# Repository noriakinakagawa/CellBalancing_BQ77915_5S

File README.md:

# CellBalancing_BQ77915_5S
5セルリチウム系バッテリのセルバランス＆過電圧過電流低電圧保護＆温度監視付回路。

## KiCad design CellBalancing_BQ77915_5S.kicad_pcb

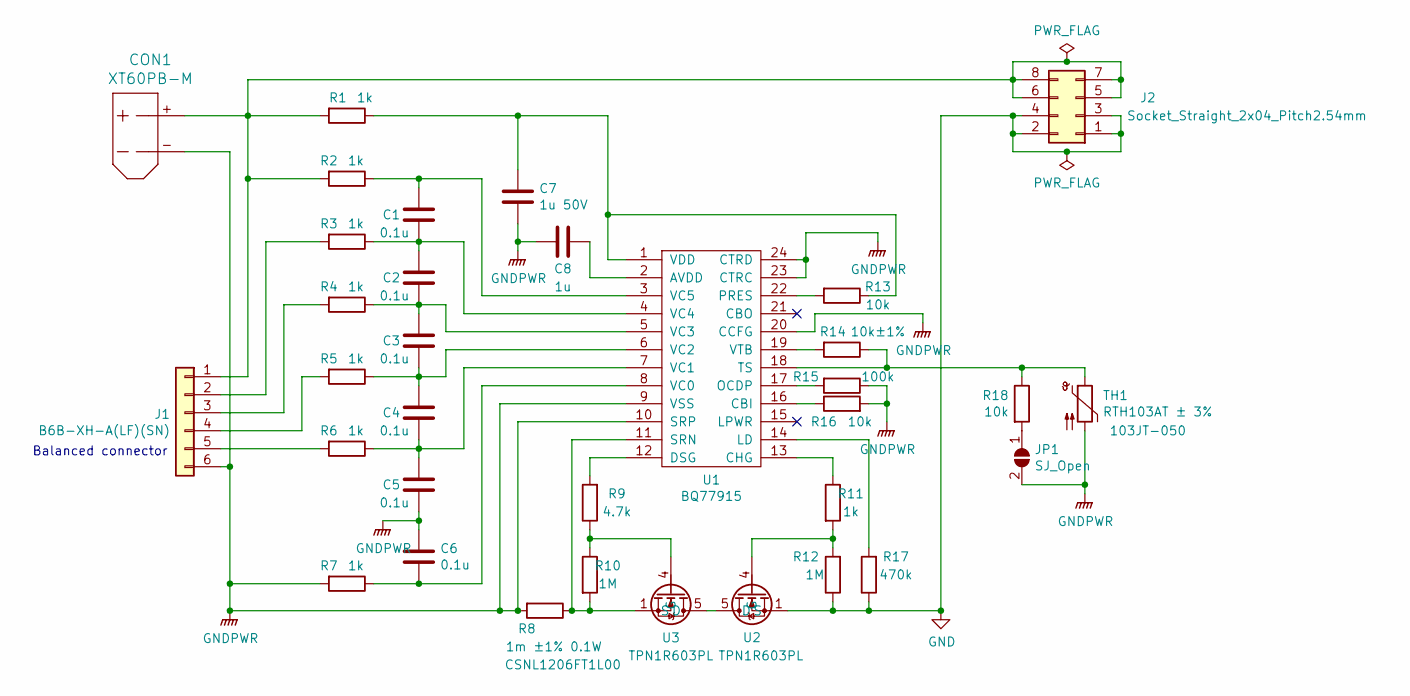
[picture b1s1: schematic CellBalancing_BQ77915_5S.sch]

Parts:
C1, C2, C3, C4, C5, C6: 0.1u; C_0603
C7: 1u 50V; C_0603
C8: 1u; C_0603
CON1: XT60PB-M
J1: B6B-XH-A(LF)(SN); JST_XH_B6B-XH-A_1x06_P2.50mm_Vertical
J2: Socket_Straight_2x04_Pitch2.54mm; Socket_Strip_Straight_2x04_Pitch2.54mm
JP1: SJ_Open; SolderJumper-2_P1.3mm_Open_RoundedPad1.0x1.5mm
R1, R2, R3, R4, R5, R6, R7, R11: 1k; R_0603
R8: 1m ±1% 0.1W; R_1206
R9: 4.7k; R_0603
R10, R12: 1M; R_0603
R13, R16, R18: 10k; R_0603
R14: 10k±1%; R_0603
R15: 100k; R_0603
R17: 470k; R_0603
TH1: RTH103AT ± 3%; SolderJumper-2_P1.3mm_Open_Pad1.0x1.5mm
U1: BQ77915; TSSOP-24_4.4x7.8mm_Pitch0.65mm
U2, U3: TPN1R603PL

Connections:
GND: J2.1, J2.2, J2.3, J2.4, R12.1, R17.1, U2.1 (S), U2.2 (S), U2.3 (S)
GNDPWR: C5.1, C6.1, C7.1, C8.1, CON1.-, J1.6, JP1.2 (B), R7.2, R8.2, R15.1, R16.2, TH1.2, U1.9 (VSS), U1.10 (SRP), U1.20 (CCFG), U1.23 (CTRC), U1.24 (CTRD)
unnamed: C1.1, C2.2, R3.1, U1.4 (VC4)
unnamed: C1.2, R2.1, U1.3 (VC5)
unnamed: C2.1, C3.2, R4.1, U1.5 (VC3)
unnamed: C3.1, C4.1, R5.1, U1.6 (VC2)
unnamed: C4.2, C5.2, R6.1, U1.7 (VC1)
unnamed: C6.2, R7.1, U1.8 (VC0)
unnamed: C7.2, R1.1, R13.1, U1.1 (VDD)
unnamed: C8.2, U1.2 (AVDD)
unnamed: CON1.+, J1.1, J2.5, J2.6, J2.7, J2.8, R1.2, R2.2
unnamed: J1.2, R3.2
unnamed: J1.3, R4.2
unnamed: J1.4, R5.2
unnamed: J1.5, R6.2
unnamed: JP1.1 (A), R18.2
unnamed: R9.2, U1.12 (DSG)
unnamed: R9.1, R10.1, U3.4 (G)
unnamed: R8.1, R10.2, U1.11 (SRN), U3.1 (S), U3.2 (S), U3.3 (S)
unnamed: R11.1, U1.13 (CHG)
unnamed: R11.2, R12.2, U2.4 (G)
unnamed: R13.2, U1.22 (PRES)
unnamed: R14.1, R18.1, TH1.1, U1.18 (TS)
unnamed: R14.2, U1.19 (VTB)
unnamed: R15.2, U1.17 (OCDP)
unnamed: R16.1, U1.16 (CBI)
unnamed: R17.2, U1.14 (LD)
unnamed: U2.5 (D), U2.6 (D), U2.7 (D), U2.8 (D), U3.5 (D), U3.6 (D), U3.7 (D), U3.8 (D)

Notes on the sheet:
Balanced connector

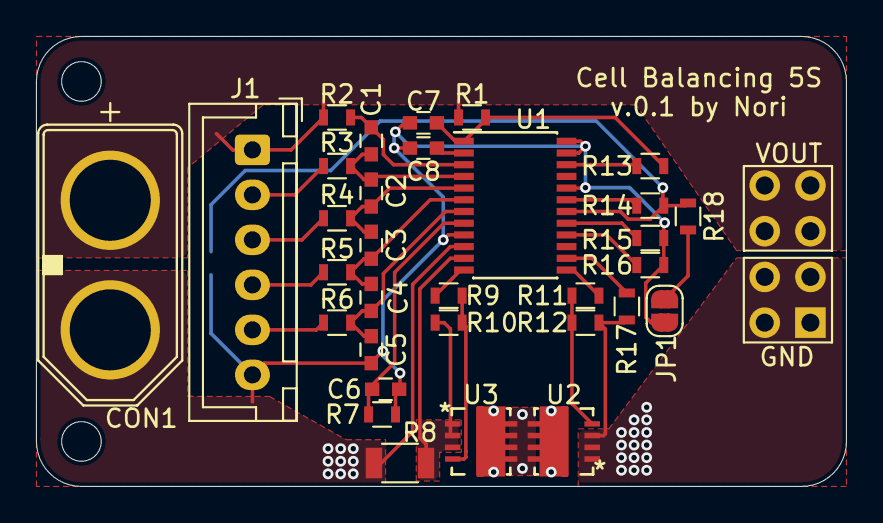
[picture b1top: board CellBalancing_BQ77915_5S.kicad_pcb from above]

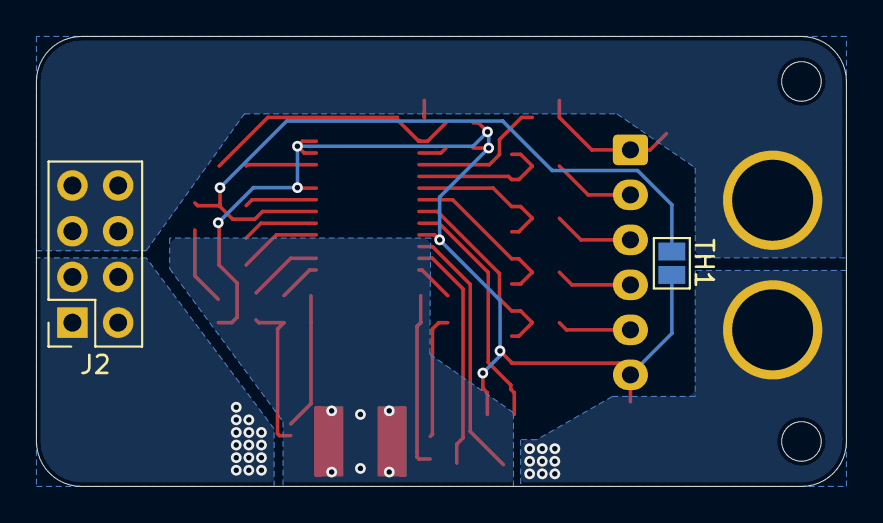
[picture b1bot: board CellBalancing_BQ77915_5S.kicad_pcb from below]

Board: 2 copper layers, 45.0 x 25.0 mm, 34 parts (2 on the bottom side), 28 nets.
